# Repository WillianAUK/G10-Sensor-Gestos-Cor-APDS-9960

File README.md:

<p align="center">

</p>

<h1 align="center">
    
</h1>

<h4 align="center"> 
	🚧  Gcontrol ⏯️ Em construção ⚠️ 🚧
</h4>

<p align="center">
 <a href="#-sobre-o-projeto">Sobre</a> •
 <a href="Setup">Setup</a> •
 <a href="Funcionalidades">Funcionalidades</a> •
 <a href="Contribuidores">Contribuidores</a> • 
 <a href="Licença">Licença</a>
</p>

## 💻 Sobre o projeto

⏯️ Gcontrol - é uma forma de acionar os controles de mídia por meio gestos identificados pelo sensor APDS-9960 

Projeto desenvolvido durante a disciplina de **Sistemas embarcados** ofertada pelo [IFPB - Campina Grande](https://www.ifpb.edu.br/campinagrande).
A disciplina faz parte do 9º semestre da grade currícular do curso de Engenharia de Computação do IFPB - Campina Grande e tem como responsável o professor [Dr. Alexandre Sales Vasconselos](http://lattes.cnpq.br/8740952344021265), que está ministrando-a no semestre 2021.1

Para videos demonstrativos e arquivos extras, acesse o o drive https://drive.google.com/drive/folders/1uk8sIaNC5tyi2TA3CVgvFQiCZkxG33-y?usp=sharing.

### Simulação

<table>
  <tr>
    <td align="center"><br /><sub><b>Execução do script de comunicação Serial do S.O. com o arduino em Python </b></sub></a><br /> </td>
    <td align="center"><br /><sub><b>Software de reprodução de mídia, utilizado como exemplo no projeto</b></sub></a><br /></td>
  </tr>
  <tr>
     <td colspan="2" align="center"><br /><sub><b>Circuito simulado no proteus</b></sub></a><br /></a></td>
  </tr>
</table>

---

## ✔️ Setup

Para obter uma cópia local instalada e funcionando, siga estas etapas simples de exemplo.

### Pré requisitos

You need Python 3.5 or later to run mypy.  You can have multiple Python
versions (2.x and 3.x) installed on the same system without problems.

Você precisa do Python 3.5 ou posterior para executar o Gcontrol. Você pode ter várias versões do Python (2.xe 3.x) instaladas no mesmo sistema sem problemas.

No Ubuntu, Mint e Debian, você pode instalar o Python 3 assim:

    $ sudo apt-get install python3 python3-pip

Para outros tipos de Linux, macOS e Windows, os pacotes estão disponíveis em

  https://www.python.org/getit/

### Instalações

1. Atualize o pip do Python
   ```sh
   python -m pip install --upgrade pip --user
   ```
2. Instale o PySerial atráves do seguinte link ou comando [PySerial](https://pythonhosted.org/pyserial/pyserial.html#installation)
   ```sh
   python -m pip install pyserial
   ```
3. Instale o PyAutoGui atrábes do seguinte link ou comando [PyAutoGui](https://pyautogui.readthedocs.io/en/latest/install.html)
   ```sh
   python -m pip install pyautogui 
   ```
4. Rode o seguinte script Python [Gcontrol_listener](./firmware/media_control/media_control.py)
5. Rode o seguinte script Arduino, com as devidas adequações a sua implementação [Gcontrol_Arduino](./firmware/controller_media/controller_media.ino)
6. Fim

<p align="right">(<a href="#top">back to top</a>)</p>

## ⚙️ Funcionalidades

- [x] Conexão do hardwaare embarcado com software de reprodução de mídias
  - [x] Implementar os protocolos de comunicação
  
- [x] Os usuários tem acesso ao sistema integrado, onde podem por meio de gestos específicos:
  - [x] Pausar 
  - [x] Despausar
  - [x] Avançar
  - [x] Retroceder 
  - [x] Aumentar volume
  - [x] Diminuir volume

---

## 👨‍💻 Desenvolvedores

<table>
  <tr>
    <td align="center"><a href="https://github.com/WillianAUK"><br /><sub><b>Willian Adriano</b></sub></a><br /><a href="https://github.com/WillianAUK" title="Willian">👨‍🚀</a></td>
    <td align="center"><a href="https://github.com/JardelBrandon"><br /><sub><b>Jardel Brandon</b></sub></a><br /><a href="https://github.com/JardelBrandon" title="Jardel">👨‍🚀</a></td>
    <td align="center"><a href="https://github.com/kvalhomanu"><br /><sub><b>Marcelo Carvalho</b></sub></a><br /><a href="https://github.com/kvalhomanu" title="Marcelo">👨‍🚀</a></td>
  </tr>
</table>

## 💪 Como contribuir para o projeto

1. Faça um **fork** do projeto.
2. Crie uma nova branch com as suas alterações: `git checkout -b my-feature`
3. Salve as alterações e crie uma mensagem de commit contando o que você fez: `git commit -m "feature: My new feature"`
4. Envie as suas alterações: `git push origin my-feature`

---

## 📝 Licença

Este projeto esta sobe a licença [MIT](./LICENSE).

---

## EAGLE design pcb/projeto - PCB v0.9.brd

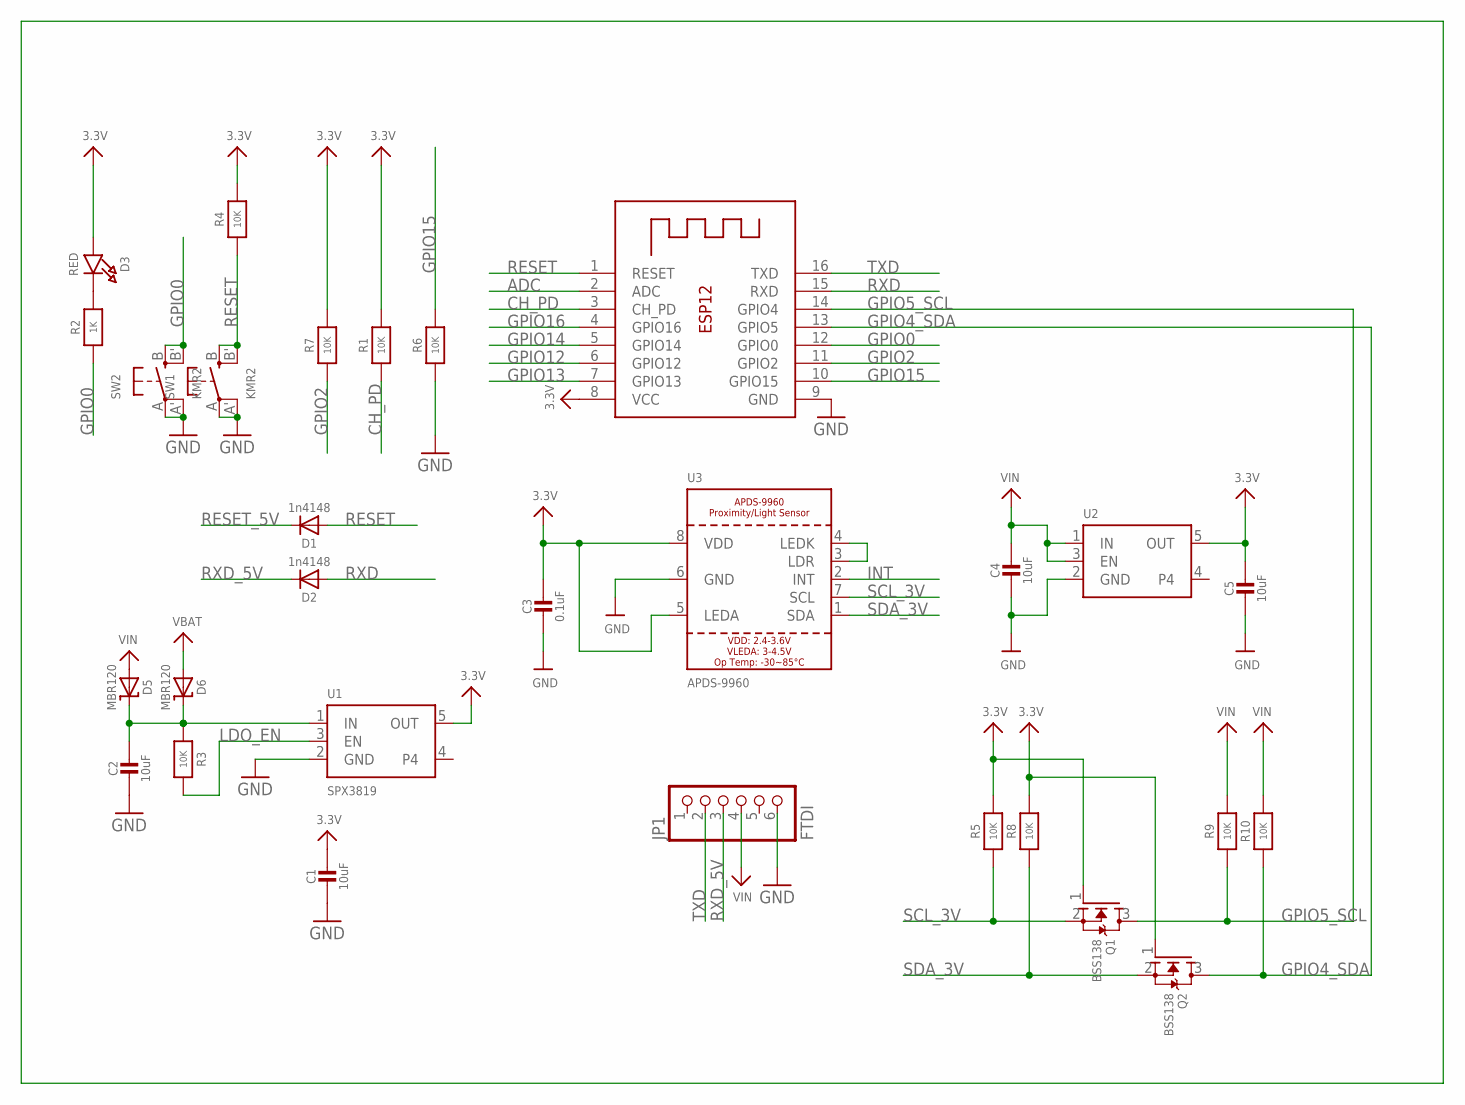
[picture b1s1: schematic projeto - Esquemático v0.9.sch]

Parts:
C1, C2, C4, C5: 10uF; 0805-NO
C3: 0.1uF; 0805-NO
D1, D2: 1n4148; SOD-323
D3: RED; CHIPLED_0805_NOOUTLINE
D5, D6: MBR120; SOD-123
JP1: FTDI; 1X06_ROUND_70
Q1, Q2: BSS138; SOT23-WIDE
R1, R3, R4, R5, R6, R7, R8, R9, R10: 10K; 0805-NO
R2: 1K; 0805-NO
SW1, SW2: KMR2; BTN_KMR2_4.6X2.8
U1: SPX3819; SOT23-5
U2: VREG_SOT23-5; SOT23-5
U3: APDS-9960
X1: ESP-12

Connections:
3.3V: C1.1, C3.1, C5.1, D3.A, Q1.1 (G), Q2.1 (G), R1.2, R4.2, R5.2, R7.2, R8.2, U1.5 (OUT), U2.5 (OUT), U3.5 (LEDA), U3.8 (VDD), X1.8 (VCC)
ADC: X1.2 (ADC)
CH_PD: R1.1, X1.3 (CH_PD)
GND: C1.2, C2.2, C3.2, C4.2, C5.2, JP1.6, R6.1, SW1.A, SW1.A' (P1), SW2.A, SW2.A' (P1), U1.2 (GND), U2.2 (GND), U3.6 (GND), X1.9 (GND)
GPIO0: R2.1, SW2.B (S), SW2.B' (S1), X1.12 (GPIO0)
GPIO2: R7.1, X1.11 (GPIO2)
GPIO4_SDA: Q2.3 (D), R10.1, X1.13 (GPIO5)
GPIO5_SCL: Q1.3 (D), R9.1, X1.14 (GPIO4)
GPIO12: X1.6 (GPIO12)
GPIO13: X1.7 (GPIO13)
GPIO14: X1.5 (GPIO14)
GPIO15: R6.2, X1.10 (GPIO15)
GPIO16: X1.4 (GPIO16)
INT: U3.2 (INT)
LDO_EN: R3.2, U1.3 (EN)
unnamed: C2.1, D5.C, D6.C, R3.1, U1.1 (IN)
unnamed: U3.3 (LDR), U3.4 (LEDK)
unnamed: D3.C, R2.2
RESET: D1.A, R4.1, SW1.B (S), SW1.B' (S1), X1.1 (RESET)
RESET_5V: D1.C
RXD: D2.A, X1.15 (RXD)
RXD_5V: D2.C, JP1.3
SCL_3V: Q1.2 (S), R5.1, U3.7 (SCL)
SDA_3V: Q2.2 (S), R8.1, U3.1 (SDA)
TXD: JP1.2, X1.16 (TXD)
VBAT: D6.A
VIN: C4.1, D5.A, JP1.4, R9.2, R10.2, U2.1 (IN), U2.3 (EN)

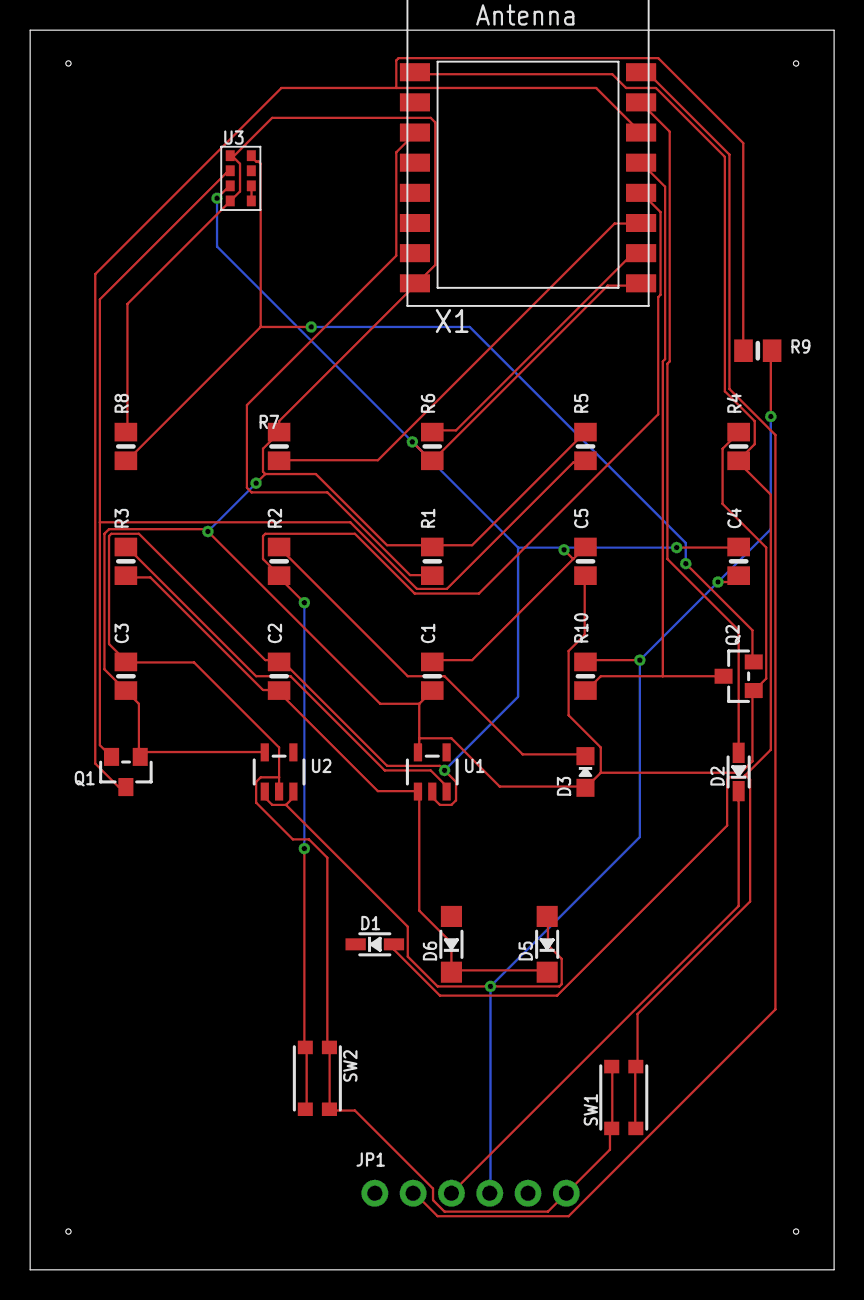
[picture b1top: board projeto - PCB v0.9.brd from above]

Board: 2 copper layers, 53.3 x 82.2 mm, 29 parts (0 on the bottom side), 19 nets.

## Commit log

2021-08-08 Adicionando diretorios e datasheets
2021-08-08 adicionando os diretórios
2021-08-09 Adicionando licença
    Criando arquivo com as regras de licença de uso do sistema
2021-08-09 Banner
    Adicionando um banner provisório do projeto
2021-08-09 Inicialização do readme
    Adicionando documentação inicial do projeto
2021-09-28 adicinando arquivos esquematico, PCB e 3D
2021-09-28 adicionando arquivos lib em produção
2021-10-11 Adicionando novos documentos e atualizando lib
2021-10-17 Imagens
    Adicionando imagens de simulação do projeto
2021-10-17 Programa para o arduino
    Adicionando arquivo de programação do arduino
2021-10-17 Programa python para Interface Arduino - S.O
    Adicionando script em python que realiza a interface comunicação do S.O com o arduino para controle do media player
2021-10-17 Simulação Proteus
    Adicionando arquivos do circuito simulado no proteus, a simulição manda os dados via interface Serial para o script em python que realiza as respectivas funcionalidades no software alvo
2021-10-17 Update README.md
    Atualizando estado atual e adicionando imagens do projeto em execução
2021-10-18 Vídeo demonstrativo
    Adicionando vídeo de demonstração do projeto em funcionamento
2021-10-18 Setup
    Adicionando um tópico de getting started, com as instruções necessárias para o setup inicial de configuração e instalações das dependências do projeto, para execução bem sucedida do projeto

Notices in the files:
parts and their libraries:
microbuilder: This work is placed in the public domain, and may be freely used for commercial and non-commercial work with the following conditions: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
